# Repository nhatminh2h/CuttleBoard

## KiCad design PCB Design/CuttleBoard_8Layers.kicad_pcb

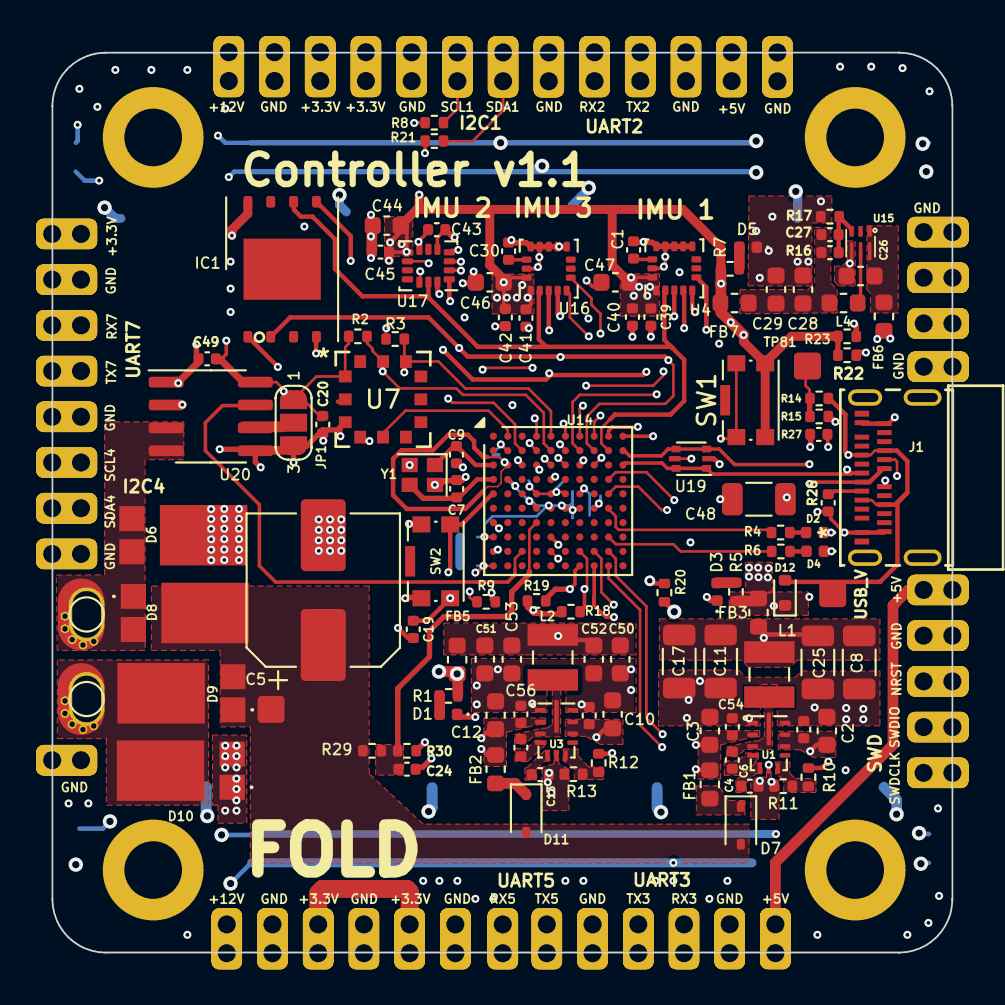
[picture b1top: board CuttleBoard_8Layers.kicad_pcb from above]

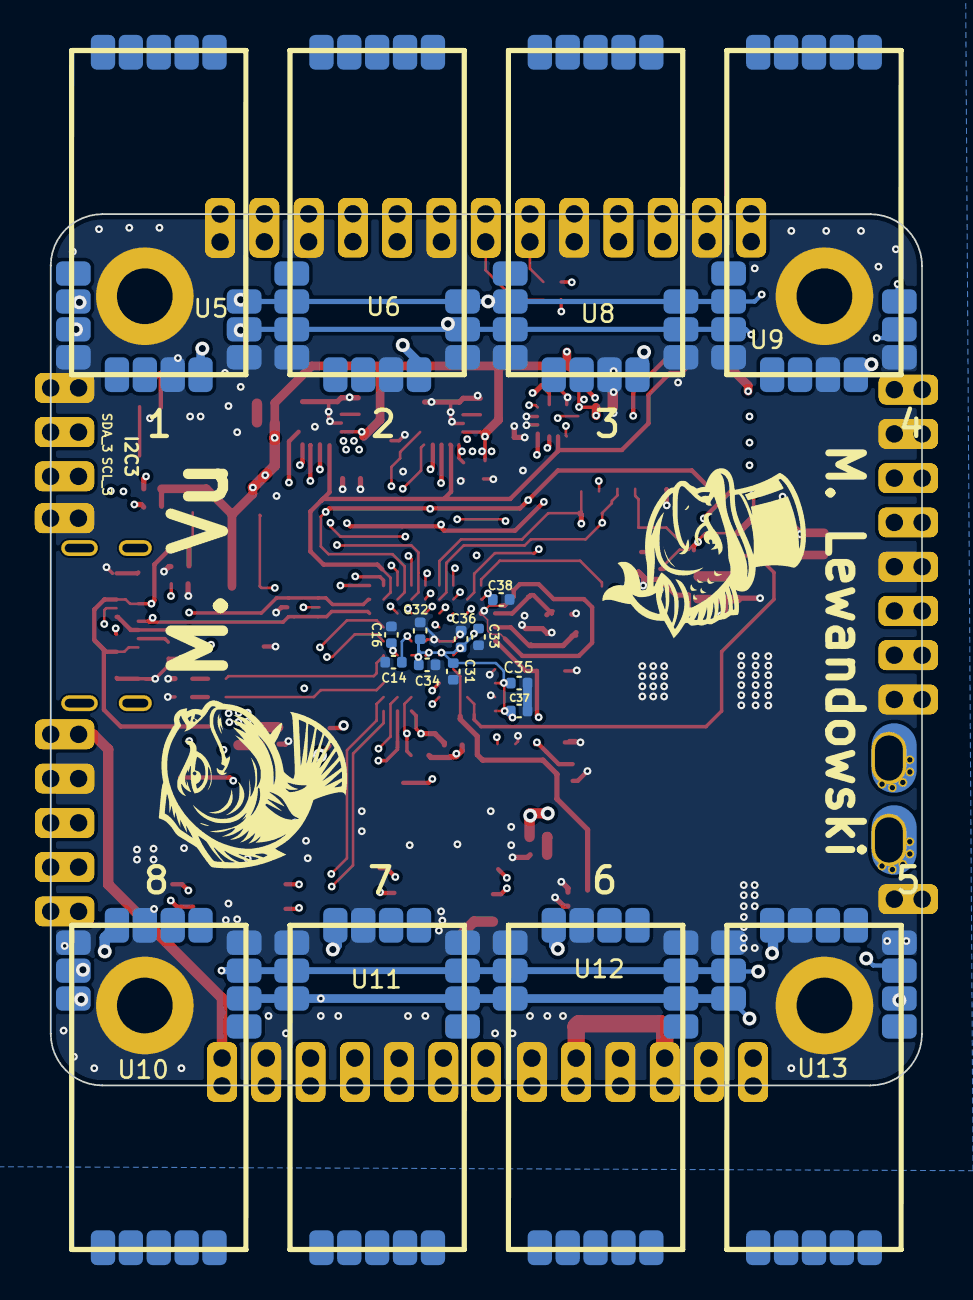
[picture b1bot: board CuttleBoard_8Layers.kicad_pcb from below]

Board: 8 copper layers, 50.0 x 50.0 mm, 180 parts (20 on the bottom side), 80 nets.

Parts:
+5V, +5V#2: Pad; Castellated_Pad_01x01_2.54mm
C1, C30: 2.2µF; C_0402_1005Metric
C2, C3, C10, C12, C26, C28, C29, C44, C46, C47, C50, C51, C52, C53: 10µF; C_0603_1608Metric
C4, C13: 1µF; C_0402_1005Metric
C5: 470uF 25V; CP_Elec_8x6.5
C6, C15, C19, C20, C24, C31, C32, C33, C34, C35, C36, C37, C38, C39, C40, C41, C42, C43, C45, C49: 100nF; C_0402_1005Metric
C7, C9: 5.6pF; C_0402_1005Metric
C8, C11, C17, C25: 22µF; C_1206_3216Metric
C14, C16: 4.7µF; C_0402_1005Metric
C18, C54, C55, C56: 220nF; C_0402_1005Metric
C27: 120pF; C_0402_1005Metric
C48: 10µF; C_1206_3216Metric
D1, D4: White; LED_0402_1005Metric
D2: Blue; LED_0402_1005Metric
D3: Red; LED_0402_1005Metric
D5: Yellow; LED_0402_1005Metric
D6, D8, D9, D10: SBRT10U50SP5-13; SBRT10U50SP513
D7, D11: PMEG3020EJ,115; D_SOD-323
D12: SBR1A30T5-7; D_SOD-523
FB1, FB2, FB3, FB5, FB6, FB7: 120R@100Mhz; L_0603_1608Metric
FISH: LOGO; smug-2
FISH#2: LOGO; smug-1
GND: Pad; Castellated_Pad_01x01_2.54mm
GND#2, GND#3, GND#4, GND#5, GND#6, GND#7, GND#8, GND#9, GND#10, GND#11, GND#12: Pad; Castellated_Pad_01x01_2.54mm
H1, H2, H3, H4: MountingHole_Pad; MountingHole_3.2mm_M3_DIN965_Pad
IC1: W25Q256JVEIQ TR; WSON-8-1EP_8x6mm_P1.27mm_EP3.4x4.3mm
J1: DX07WH24JA3R1200; DX07WH24JA3R1200_JAE
JP1: SolderJumper_3_Open; SolderJumper-3_P1.3mm_Open_RoundedPad1.0x1.5mm_NumberLabels
L1: 2.2µH; L_Wuerth_MAPI-2506
L2: 3.3µH; L_Wuerth_MAPI-2506
L4: 470nH; L_0603_1608Metric
NRST: Pad; Castellated_Pad_01x01_2.54mm
R1: 4k7; R_0402_1005Metric
R2, R3, R8, R18, R19, R20, R21, R22, R23, R29: 10k; R_0402_1005Metric
R4, R6: 560R; R_0402_1005Metric
R5: 1k5; R_0402_1005Metric
R7: 680R; R_0402_1005Metric
R9: 2k2; R_0402_1005Metric
R10, R12, R17: 100k; R_0402_1005Metric
R11: 24k9; R_0402_1005Metric
R13: 9.09k; R_0402_1005Metric
R14: 470R; R_0402_1005Metric
R15, R30: 1k; R_0402_1005Metric
R16: 453k; C_0402_1005Metric
R26, R27: 5.1K; C_0402_1005Metric
RX3, RX5: Pad; Castellated_Pad_01x01_2.54mm
SCL_3: Pad; Castellated_Pad_01x01_2.54mm
SDA1: Pad; Castellated_Pad_01x01_2.54mm
SDA_3: Pad; Castellated_Pad_01x01_2.54mm
SW1, SW2: SW_Push; SW_Push_1P1T-SH_NO_CK_KMR2xxG
SWDCLK: Pad; Castellated_Pad_01x01_2.54mm
SWDIO: Pad; Castellated_Pad_01x01_2.54mm
TP1: BattPad+; batt_conn_oval
TP2: BattPad-; batt_conn_oval
TP3, TP4, TP7, TP8, TP9, TP10, TP11, TP12, TP21, TP35, TP36, TP39, TP40, TP41, TP42, TP44, TP45, TP47, TP48: Pad; Castellated_Pad_01x01_2.54mm
TP6, TP81, TP88: Pad; chonker_TestPoint_Pad_1.5x1.5mm
TX3, TX5, TX7: Pad; Castellated_Pad_01x01_2.54mm
U1, U3: LMR33630CQRNX; Texas_RNX0012B
U4, U16: ICM-20602; LGA-16_3x3mm_P0.5mm_LayoutBorder3x5y
U5, U6, U8, U9, U10, U11, U12, U13: uDriver_I2C
U7: MPRLS0025PA00001A; MPRLS_HNW
U14: STM32H743VIHx; TFBGA-100_8x8mm_Layout10x10_P0.8mm
U15: TPS62824ADMQ; VSON_HR6
U17: LGA-14_3x2.5mm_P0.5mm_LayoutBorder3x4y
U19: USBLC6-2P6; SOT-666
U20: ACS722xLCTR-10AB; SOIC-8_3.9x4.9mm_P1.27mm
Y1: NX2016SA; Crystal_SMD_2016-4Pin_2.0x1.6mm

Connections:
+3.3V: C20.1, C31.1, C32.1, C33.1, C34.1, C35.1, C36.1, C37.1, C38.1, C39.1, C40.1, C41.1, C42.1, C43.1, C44.1, C45.1, C46.1, C47.1, C49.1, FB7.1, IC1.8 (VCC), JP1.1 (A), R2.1, R3.1, R7.1, R8.1, R18.1, R19.1, R20.1, R21.1, R22.1, R23.1, SW1.2, TP7.1, TP8.1, TP9.1, TP44.1, TP45.1, U4.1 (VDDIO), U4.16 (VDD), U7.12 (VDD), U14.B2 (VBAT), U14.D2 (VDD), U14.F4 (VDDLDO), U14.F5 (VDD), U14.F6 (VDD33_USB), U14.F7 (PDR_ON), U14.H1 (VDDA), U14.K1 (VDD), U16.1 (VDDIO), U16.16 (VDD), U17.5 (VDD_IO), U17.8 (VDD), U20.8 (VCC)
+5V: +5V.1, +5V#2.1, D12.1 (K), FB3.1, FB6.1, R5.1, TP36.1
+12V: FB5.1, R1.1, TP3.1, TP4.1, U5.1 (V_MOTOR), U6.1 (V_MOTOR), U8.1 (V_MOTOR), U9.1 (V_MOTOR), U10.1 (V_MOTOR), U11.1 (V_MOTOR), U12.1 (V_MOTOR), U13.1 (V_MOTOR)
+BATT: C5.1, D7.2 (A), D8.3 (K), D9.1 (A_1), D9.2 (A_2), D11.2 (A), R29.1, TP6.1
/BattPad-: D6.1 (A_1), D6.2 (A_2), D8.1 (A_1), D8.2 (A_2), TP2.1, U20.3 (IP-), U20.4 (IP-)
/Coil+: D9.3 (K), D10.3 (K), TP1.1
BOOT0: R9.1, SW1.1, U14.D5 (BOOT0)
CS_FLASH: IC1.1 (CS#), U14.C3 (PE4)
CS_IMU1: U4.5 (~CS), U14.C7 (PD3)
CS_IMU2: U14.A7 (PB3), U16.5 (~CS)
CS_IMU3: U14.A6 (PB4), U17.12 (CS)
EOC_PRESSURE: U7.8 (EOC), U14.A2 (PC13)
GND: C1.2, C2.2, C3.2, C4.2, C5.2, C7.2, C8.2, C9.2, C10.2, C11.2, C12.2, C13.2, C14.2, C16.2, C17.2, C18.2, C19.2, C20.2, C24.2, C25.2, C26.2, C28.2, C29.2, C30.2, C31.2, C32.2, C33.2, C34.2, C35.2, C36.2, C37.2, C38.2, C39.2, C40.2, C41.2, C42.2, C43.2, C44.2, C45.2, C46.2, C47.2, C48.2, C49.2, C50.2, C51.2, C52.2, C53.2, C54.2, C55.2, C56.2, D1.1 (K), D2.1 (K), D3.1 (K), D4.1 (K), D5.1 (K), D6.3 (K), D10.1 (A_1), D10.2 (A_2), GND.1, GND#2.1, GND#3.1, GND#4.1, GND#5.1, GND#6.1, GND#7.1, GND#8.1, GND#9.1, GND#10.1, GND#11.1, GND#12.1, H1.1, H2.1, H3.1, H4.1, IC1.4 (VSS), J1.A1 (GND), J1.A12 (GND), J1.B1 (GND), J1.B12 (GND), JP1.3 (B), R9.2, R11.2, R13.2, R15.2, R17.2, R26.1, R27.1, R30.2, SW2.1, TP35.1, TP39.1, TP40.1, TP41.1, TP42.1, U1.1 (PGND), U1.6 (AGND), U1.11 (PGND), U3.1 (PGND), U3.6 (AGND), U3.11 (PGND), U4.9 (GND), U4.10 (GND), U4.11 (GND), U4.12 (GND), U4.13 (GND), U4.15 (GND), U5.2 (GND), U5.5 (GND), U5.16 (GND), U6.2 (GND), U6.5 (GND), U6.16 (GND), U7.10 (VSS), U8.2 (GND), U8.5 (GND), U8.16 (GND), U9.2 (GND), U9.5 (GND), U9.16 (GND), U10.2 (GND), U10.5 (GND), U10.16 (GND), U11.2 (GND), U11.5 (GND), U11.16 (GND), U12.2 (GND), U12.5 (GND), U12.16 (GND), U13.2 (GND), U13.5 (GND), U13.16 (GND), U14.C2 (VSS), U14.E4 (VSS), U14.E5 (VSS), U14.E6 (VSS), U14.G1 (VSSA), U14.J1 (VSS), U15.4 (GND), U16.9 (GND), U16.10 (GND), U16.11 (GND), U16.12 (GND), U16.13 (GND), U16.15 (GND), U17.2 (RES), U17.3 (RES), U17.7 (GND), U19.2 (GND), U20.1 (IP+), U20.2 (IP+), U20.5 (GND), Y1.2, Y1.4
I2C1_SCL: R8.2, TP21.1, U14.B4 (PB8)
I2C1_SDA: R21.2, SDA1.1, U14.A4 (PB9)
I2C2_SCL: R18.2, U5.6 (SCL), U5.15 (SCL), U6.6 (SCL), U6.15 (SCL), U8.6 (SCL), U8.15 (SCL), U9.6 (SCL), U9.15 (SCL), U10.6 (SCL), U10.15 (SCL), U11.6 (SCL), U11.15 (SCL), U12.6 (SCL), U12.15 (SCL), U13.6 (SCL), U13.15 (SCL), U14.J7 (PB10)
I2C2_SDA: R19.2, U5.7 (SDA), U5.14 (SDA), U6.7 (SDA), U6.14 (SDA), U8.7 (SDA), U8.14 (SDA), U9.7 (SDA), U9.14 (SDA), U10.7 (SDA), U10.14 (SDA), U11.7 (SDA), U11.14 (SDA), U12.7 (SDA), U12.14 (SDA), U13.7 (SDA), U13.14 (SDA), U14.K7 (PB11)
I2C3_SCL: R22.2, SCL_3.1, U14.D9 (PA8)
I2C3_SDA: R23.2, SDA_3.1, U14.E9 (PC9)
I2C4_SCL: R2.2, TP47.1, U7.2 (MOSI/SDA), U14.B5 (PB6)
I2C4_SDA: R3.2, TP48.1, U7.3 (SCLK/SCL), U14.A5 (PB7)
INT1_IMU3: U14.C4 (PE1), U17.4 (INT1)
INT2_IMU3: U14.C5 (PB5), U17.9 (INT2)
INT_IMU1: U4.6 (INT), U14.B7 (PD2)
INT_IMU2: U14.A8 (PA15), U16.6 (INT)
LED_BL: R6.1, U14.H9 (PD10)
LED_WT: R4.1, U14.F9 (PC8)
NRST: C19.1, NRST.1, R20.2, SW2.2, U14.E1 (NRST)
unnamed: C8.1, C11.1, C17.1, C25.1, FB3.2, L1.2, R10.1
unnamed: C14.1, U14.E7 (VCAP)
unnamed: C16.1, U14.F8 (VCAP)
unnamed: C27.1, C28.1, C29.1, FB7.2, L4.2, R16.1
unnamed: C50.1, C51.1, C52.1, C53.1, FB5.2, L2.2, R12.1
unnamed: D1.2 (A), R1.2
unnamed: D2.2 (A), R4.2
unnamed: D3.2 (A), R5.2
unnamed: D4.2 (A), R6.2
unnamed: D5.2 (A), R7.2
unnamed: D7.1 (K), FB1.1
unnamed: D11.1 (K), FB2.1
unnamed: J1.A5 (CC1), R26.2
unnamed: J1.B5 (CC2), R27.2
unnamed: JP1.2 (C), U20.6 (BW_SEL)
unnamed: R14.2, R15.1, TP81.1
unnamed: C6.2, U1.4 (BOOT)
unnamed: C2.1, C3.1, C18.1, C54.1, FB1.2, U1.2 (VIN), U1.9 (EN), U1.10 (VIN)
unnamed: R10.2, R11.1, U1.7 (FB)
unnamed: C6.1, L1.1, U1.3 (NC), U1.12 (SW)
unnamed: C4.1, U1.5 (VCC)
unnamed: C15.2, U3.4 (BOOT)
unnamed: C10.1, C12.1, C55.1, C56.1, FB2.2, U3.2 (VIN), U3.9 (EN), U3.10 (VIN)
unnamed: R12.2, R13.1, U3.7 (FB)
unnamed: C15.1, L2.1, U3.3 (NC), U3.12 (SW)
unnamed: C13.1, U3.5 (VCC)
unnamed: C1.1, U4.14 (REGOUT)
unnamed: C26.1, FB6.2, U15.1 (EN), U15.6 (VIN)
unnamed: C27.2, R16.2, R17.1, U15.3 (FB)
unnamed: L4.1, U15.5 (SW)
unnamed: C30.1, U16.14 (REGOUT)
OSC_IN: C9.1, U14.C1 (PH0), Y1.1
OSC_OUT: C7.1, U14.D1 (PH1), Y1.3
RES_PRESSURE: U7.9 (RES), U14.B3 (PE3)
SPI3_MISO: IC1.2 (SO__/_IO_1), U4.4 (SAO/SD0), U14.B8 (PC11), U16.4 (SAO/SD0), U17.1 (SDO)
SPI3_MOSI: IC1.5 (SI_/_IO_0), U4.3 (SDA/SDI), U14.C8 (PC12), U16.3 (SDA/SDI), U17.14 (SDA)
SPI3_SCK: IC1.6 (SCK), U4.2 (SCL/SPC), U14.B9 (PC10), U16.2 (SCL/SPC), U17.13 (SCL)
SWDCLK: SWDCLK.1, U14.A9 (PA14)
SWDIO: SWDIO.1, U14.A10 (PA13)
UART2_RX: TP10.1, U14.C6 (PD6)
UART2_TX: TP11.1, U14.B6 (PD5)
UART3_RX: RX3.1, U14.J9 (PD9)
UART3_TX: TX3.1, U14.K9 (PD8)
UART5_RX: RX5.1, U14.K8 (PB12)
UART5_TX: TX5.1, U14.J8 (PB13)
UART7_RX: TP12.1, U14.H5 (PE7)
UART7_TX: TX7.1, U14.J5 (PE8)
USB_D+: J1.A6 (D+), J1.B6 (D+), U14.B10 (PA12), U19.3 (I/O2), U19.4 (I/O2)
USB_D-: J1.A7 (D-), J1.B7 (D-), U14.C10 (PA11), U19.1 (I/O1), U19.6 (I/O1)
USB_VBUS: C48.1, D12.2 (A), J1.A4 (VBUS), J1.A9 (VBUS), J1.B4 (VBUS), J1.B9 (VBUS), R14.1, TP88.1, U19.5 (VBUS)
VSense: C24.1, R29.2, R30.1, U14.G4 (PC4)
curr_sig: U14.J3 (PA6), U20.7 (VIOUT)

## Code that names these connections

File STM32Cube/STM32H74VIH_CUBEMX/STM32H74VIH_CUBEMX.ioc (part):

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Mcu.Name=STM32H743V(G-I)Hx
Mcu.Package=TFBGA100
Mcu.UserName=STM32H743VIHx
PA11.Mode=Host_Only
PA11.Signal=USB_OTG_FS_DM
PA12.Mode=Host_Only
PA12.Signal=USB_OTG_FS_DP
PA13\ (JTMS/SWDIO).Mode=Serial_Wire
PA13\ (JTMS/SWDIO).Signal=DEBUG_JTMS-SWDIO
PA14\ (JTCK/SWCLK).Mode=Serial_Wire
PA14\ (JTCK/SWCLK).Signal=DEBUG_JTCK-SWCLK
PA15\ (JTDI).GPIOParameters=GPIO_Label
PA15\ (JTDI).GPIO_Label=INT_IMU2
PA15\ (JTDI).Signal=GPIO_Input
PA6.GPIOParameters=GPIO_Label
PA6.GPIO_Label=curr_sig
PA6.Signal=ADCx_INP3
PA8.Mode=I2C
PA8.Signal=I2C3_SCL
PB10.Mode=I2C
PB10.Signal=I2C2_SCL
PB11.Mode=I2C
PB11.Signal=I2C2_SDA
PB12.Mode=Asynchronous
PB12.Signal=UART5_RX
PB13.Mode=Asynchronous
PB13.Signal=UART5_TX
PB14.Signal=USB_OTG_HS_DM
PB15.Signal=USB_OTG_HS_DP
PB3\ (JTDO/TRACESWO).GPIOParameters=GPIO_Label
PB3\ (JTDO/TRACESWO).GPIO_Label=CS_IMU2
PB3\ (JTDO/TRACESWO).Signal=GPIO_Output
PB4\ (NJTRST).GPIOParameters=GPIO_Label
PB4\ (NJTRST).GPIO_Label=CS_IMU3
PB4\ (NJTRST).Signal=GPIO_Output
PB5.GPIOParameters=GPIO_Label
PB5.GPIO_Label=INT2_IMU3
PB5.Signal=GPIO_Input
PB6.Mode=I2C
PB6.Signal=I2C4_SCL
PB7.Mode=I2C
PB7.Signal=I2C4_SDA
PB8.Mode=I2C
PB8.Signal=I2C1_SCL
PB9.Mode=I2C
PB9.Signal=I2C1_SDA
PC10.Mode=Full_Duplex_Master
PC10.Signal=SPI3_SCK
PC11.Mode=Full_Duplex_Master
PC11.Signal=SPI3_MISO
PC12.Mode=Full_Duplex_Master
PC12.Signal=SPI3_MOSI
PC13.GPIOParameters=GPIO_Label
PC13.GPIO_Label=EOC_PRESSURE
PC13.Signal=GPIO_Output
PC4.Signal=ADCx_INP4
PC8.GPIOParameters=GPIO_Label
PC8.GPIO_Label=LED_WT
PC8.Signal=GPIO_Output
PC9.Mode=I2C
PC9.Signal=I2C3_SDA
PD2.GPIOParameters=GPIO_Label
PD2.GPIO_Label=INT_MUL1
PD2.Signal=GPIO_Input
PD3.GPIOParameters=GPIO_Label
PD3.GPIO_Label=CS_IMU1
PD3.Signal=GPIO_Output
PD5.Mode=Asynchronous
PD5.Signal=USART2_TX
PD6.Mode=Asynchronous
PD6.Signal=USART2_RX
PD8.Mode=Asynchronous
PD8.Signal=USART3_TX
PD9.Mode=Asynchronous
PD9.Signal=USART3_RX
PE1.GPIOParameters=GPIO_Label
PE1.GPIO_Label=INT1_IMU3
PE1.Signal=GPIO_Input
PE3.GPIOParameters=GPIO_Label
PE3.GPIO_Label=RES_PRESSURE
PE3.Signal=GPIO_Output
PE4.GPIOParameters=GPIO_Label
PE4.GPIO_Label=FLASH_CS
PE4.Signal=GPIO_Output
PE7.Mode=Asynchronous
PE7.Signal=UART7_RX
PE8.Mode=Asynchronous
PE8.Signal=UART7_TX
PH0-OSC_IN\ (PH0).Mode=HSE-External-Oscillator
PH0-OSC_IN\ (PH0).Signal=RCC_OSC_IN
PH1-OSC_OUT\ (PH1).Mode=HSE-External-Oscillator
PH1-OSC_OUT\ (PH1).Signal=RCC_OSC_OUT
RCC.SYSCLKFreq_VALUE=64000000
board=custom

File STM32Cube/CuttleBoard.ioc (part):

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Mcu.Name=STM32H735VGHx
Mcu.Package=TFBGA100
Mcu.UserName=STM32H735VGHx
PA10.Signal=GPIO_Output
PA11.Mode=Device_Only_FS
PA11.Signal=USB_OTG_HS_DM
PA12.Mode=Device_Only_FS
PA12.Signal=USB_OTG_HS_DP
PA13(JTMS/SWDIO).Mode=Serial_Wire
PA13(JTMS/SWDIO).Signal=DEBUG_JTMS-SWDIO
PA14(JTCK/SWCLK).Mode=Serial_Wire
PA14(JTCK/SWCLK).Signal=DEBUG_JTCK-SWCLK
PA15(JTDI).Signal=SPI3_NSS
PA6.GPIOParameters=GPIO_Label
PA6.GPIO_Label=curr_sig
PA6.Signal=ADCx_INP3
PA8.GPIOParameters=GPIO_Label
PA8.GPIO_Label=LED_WT
PA8.Signal=GPIO_Output
PA9.Signal=GPIO_Analog
PB10.Mode=I2C
PB10.Signal=I2C2_SCL
PB11.Mode=I2C
PB11.Signal=I2C2_SDA
PB6.Mode=I2C
PB6.Signal=I2C1_SCL
PB7.Mode=I2C
PB7.Signal=I2C1_SDA
PB8.Mode=I2C
PB8.Signal=I2C4_SCL
PB9.Mode=I2C
PB9.Signal=I2C4_SDA
PC10.Mode=Full_Duplex_Master
PC10.Signal=SPI3_SCK
PC11.Mode=Full_Duplex_Master
PC11.Signal=SPI3_MISO
PC12.Mode=Full_Duplex_Master
PC12.Signal=SPI3_MOSI
PC4.Signal=ADCx_INP4
PC9.Signal=I2C5_SDA
PD0.Mode=Asynchronous
PD0.Signal=UART4_RX
PD1.Mode=Asynchronous
PD1.Signal=UART4_TX
PD10.GPIOParameters=GPIO_Label
PD10.GPIO_Label=LED_BL
PD10.Signal=GPIO_Output
PD14.Mode=Asynchronous
PD14.Signal=UART9_RX
PD15.Mode=Asynchronous
PD15.Signal=UART9_TX
PD2.GPIOParameters=GPIO_Label
PD2.GPIO_Label=CS_IMU1
PD2.Signal=GPIO_Output
PD3.GPIOParameters=GPIO_Label
PD3.GPIO_Label=INT_IMU1
PD3.Signal=GPIO_Input
PD8.Mode=Asynchronous
PD8.Signal=USART3_TX
PD9.Mode=Asynchronous
PD9.Signal=USART3_RX
PE4.GPIOParameters=GPIO_Label
PE4.GPIO_Label=FLASH_CS
PE4.Signal=GPIO_Output
PE5.GPIOParameters=GPIO_Label
PE5.GPIO_Label=RES_PRESSURE
PE5.Signal=GPIO_Output
PE6.GPIOParameters=GPIO_Label
PE6.GPIO_Label=EOC_PRESSURE
PE6.Signal=GPIO_Output
PE7.Mode=Asynchronous
PE7.Signal=UART7_RX
PE8.Mode=Asynchronous
PE8.Signal=UART7_TX
PH0-OSC_IN.Mode=HSE-External-Oscillator
PH0-OSC_IN.Signal=RCC_OSC_IN
PH1-OSC_OUT.Mode=HSE-External-Oscillator
PH1-OSC_OUT.Signal=RCC_OSC_OUT
RCC.SYSCLKFreq_VALUE=500000000
RCC.SYSCLKSource=RCC_SYSCLKSOURCE_PLLCLK
board=custom

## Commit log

2024-05-11 Initial Commit of CuttleBoard
2024-05-14 Restructured files, added stm32 config
2024-05-14 cleanup
2024-05-20 redone schematics for H743VIT
2024-05-20 good progress, needs checking, 14 violations to fix
2024-05-21 redid some of the pins for STM32CubeMX
2024-05-21 Revert "STM32H743 first version"
2024-05-21 readded the files after revert, sad
2024-05-21 Fixed castellated edge and some vias
2024-05-21 fixed errors/warnings, looks OK, needs doublechecking
2024-05-22 via size 0.35mm to 0.45mm
2024-05-26 finished BOM for JLCPCB, switched 0201 for 0402, cleaned up silkscreen
2024-05-26 final push
